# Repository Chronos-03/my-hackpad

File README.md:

# My Custom Hackpad

**Description:** This is a custom 4x2 macropad powered by a Seeed Studio XIAO RP2040. It features a rotary encoder, a 0.91" OLED display, per-key RGB backlighting, and underglow, all wrapped in a custom 3D-printed snap-fit case.

## 📸 Overall Design

## ⚡ KiCAD Schematic & PCB Layout

## 🛠️ Case Assembly & Fit

## 📋 Bill of Materials (BOM)
* 1x Seeed Studio XIAO RP2040
* 8x Mechanical Key Switches (e.g., Gateron)
* 1x 0.91" I2C OLED Display (4-pin)
* 1x Alps Rotary Encoder
* 8x SK6812MINI-E RGB LEDs (Per-key backlight)
* 4x RGB LEDs (Underglow)
* 9x 1N4148 Diodes
* 1x 3D Printed Top Plate
* 1x 3D Printed Bottom Case

## 📐 Hardware Specifications & Layout Map

| Component Category | Designation | Description / Model | X Position (mm) | Y Position (mm) |
| :--- | :--- | :--- | :--- | :--- |
| **Microcontroller** | `U1` | Seeed Studio XIAO | 50.0 | 12.0 |
| **Display Header** | `J1` | 4-Pin OLED (`GND-VCC-SCL-SDA`) | 14.5 | 16.5 |
| **Rotary Encoder** | `SW9` | Alps Rotary Encoder | 79.0 | 19.0 |
| **Key Switch** | `SW1` | Mechanical Key Switch (R1, C1) | 20.0 | 45.35 |
| **Key Switch** | `SW2` | Mechanical Key Switch (R1, C2) | 42.0 | 45.35 |
| **Key Switch** | `SW3` | Mechanical Key Switch (R1, C3) | 64.0 | 45.35 |
| **Key Switch** | `SW4` | Mechanical Key Switch (R1, C4) | 86.0 | 45.35 |
| **Key Switch** | `SW5` | Mechanical Key Switch (R2, C1) | 20.0 | 74.35 |
| **Key Switch** | `SW6` | Mechanical Key Switch (R2, C2) | 42.0 | 74.35 |
| **Key Switch** | `SW7` | Mechanical Key Switch (R2, C3) | 64.0 | 74.35 |
| **Key Switch** | `SW8` | Mechanical Key Switch (R2, C4) | 86.0 | 74.35 |
| **Backlight LED** | `D2` | SK6812MINI-E (SW1) | 16.0 | 38.0 |
| **Backlight LED** | `D3` | SK6812MINI-E (SW2) | 39.0 | 38.0 |
| **Backlight LED** | `D4` | SK6812MINI-E (SW3) | 61.0 | 38.0 |
| **Backlight LED** | `D5` | SK6812MINI-E (SW4) | 85.0 | 38.0 |
| **Backlight LED** | `D6` | SK6812MINI-E (SW5) | 16.0 | 67.0 |
| **Backlight LED** | `D7` | SK6812MINI-E (SW6) | 39.0 | 67.0 |
| **Backlight LED** | `D8` | SK6812MINI-E (SW7) | 61.0 | 67.0 |
| **Backlight LED** | `D9` | SK6812MINI-E (SW8) | 85.0 | 67.0 |
| **Underglow LED** | `D1` | Underglow LED 1 | 14.0 | 5.0 |
| **Underglow LED** | `D10` | Underglow LED 2 | 85.0 | 5.0 |
| **Underglow LED** | `D11` | Underglow LED 3 | 16.0 | 5.0 |
| **Underglow LED** | `D12` | Underglow LED 4 | 85.0 | 95.0 |
| **Matrix Diode** | `Diode 1` | 1N4148 Diode 1 | 18.0 | 21.0 |
| **Matrix Diode** | `Diode 2` | 1N4148 Diode 2 | 18.0 | 24.0 |
| **Matrix Diode** | `Diode 3` | 1N4148 Diode 3 | 18.0 | 27.0 |
| **Matrix Diode** | `Diode 4` | 1N4148 Diode 4 | 18.0 | 30.0 |
| **Matrix Diode** | `Diode 5` | 1N4148 Diode 5 | 35.8 | 21.6 |
| **Matrix Diode** | `Diode 6` | 1N4148 Diode 6 | 35.8 | 24.6 |
| **Matrix Diode** | `Diode 7` | 1N4148 Diode 7 | 35.8 | 27.6 |
| **Matrix Diode** | `Diode 8` | 1N4148 Diode 8 | 35.8 | 30.6 |
| **Matrix Diode** | `Diode 9` | 1N4148 Diode 9 | 64.0 | 25.0 |
| **Mounting Hole** | `H1` | Top-Left Mounting Hole | 5.0 | 5.0 |
| **Mounting Hole** | `H2` | Top-Right Mounting Hole | 95.0 | 5.0 |
| **Mounting Hole** | `H3` | Bottom-Left Mounting Hole | 5.0 | 95.0 |
| **Mounting Hole** | `H4` | Bottom-Right Mounting Hole | 95.0 | 95.0 |

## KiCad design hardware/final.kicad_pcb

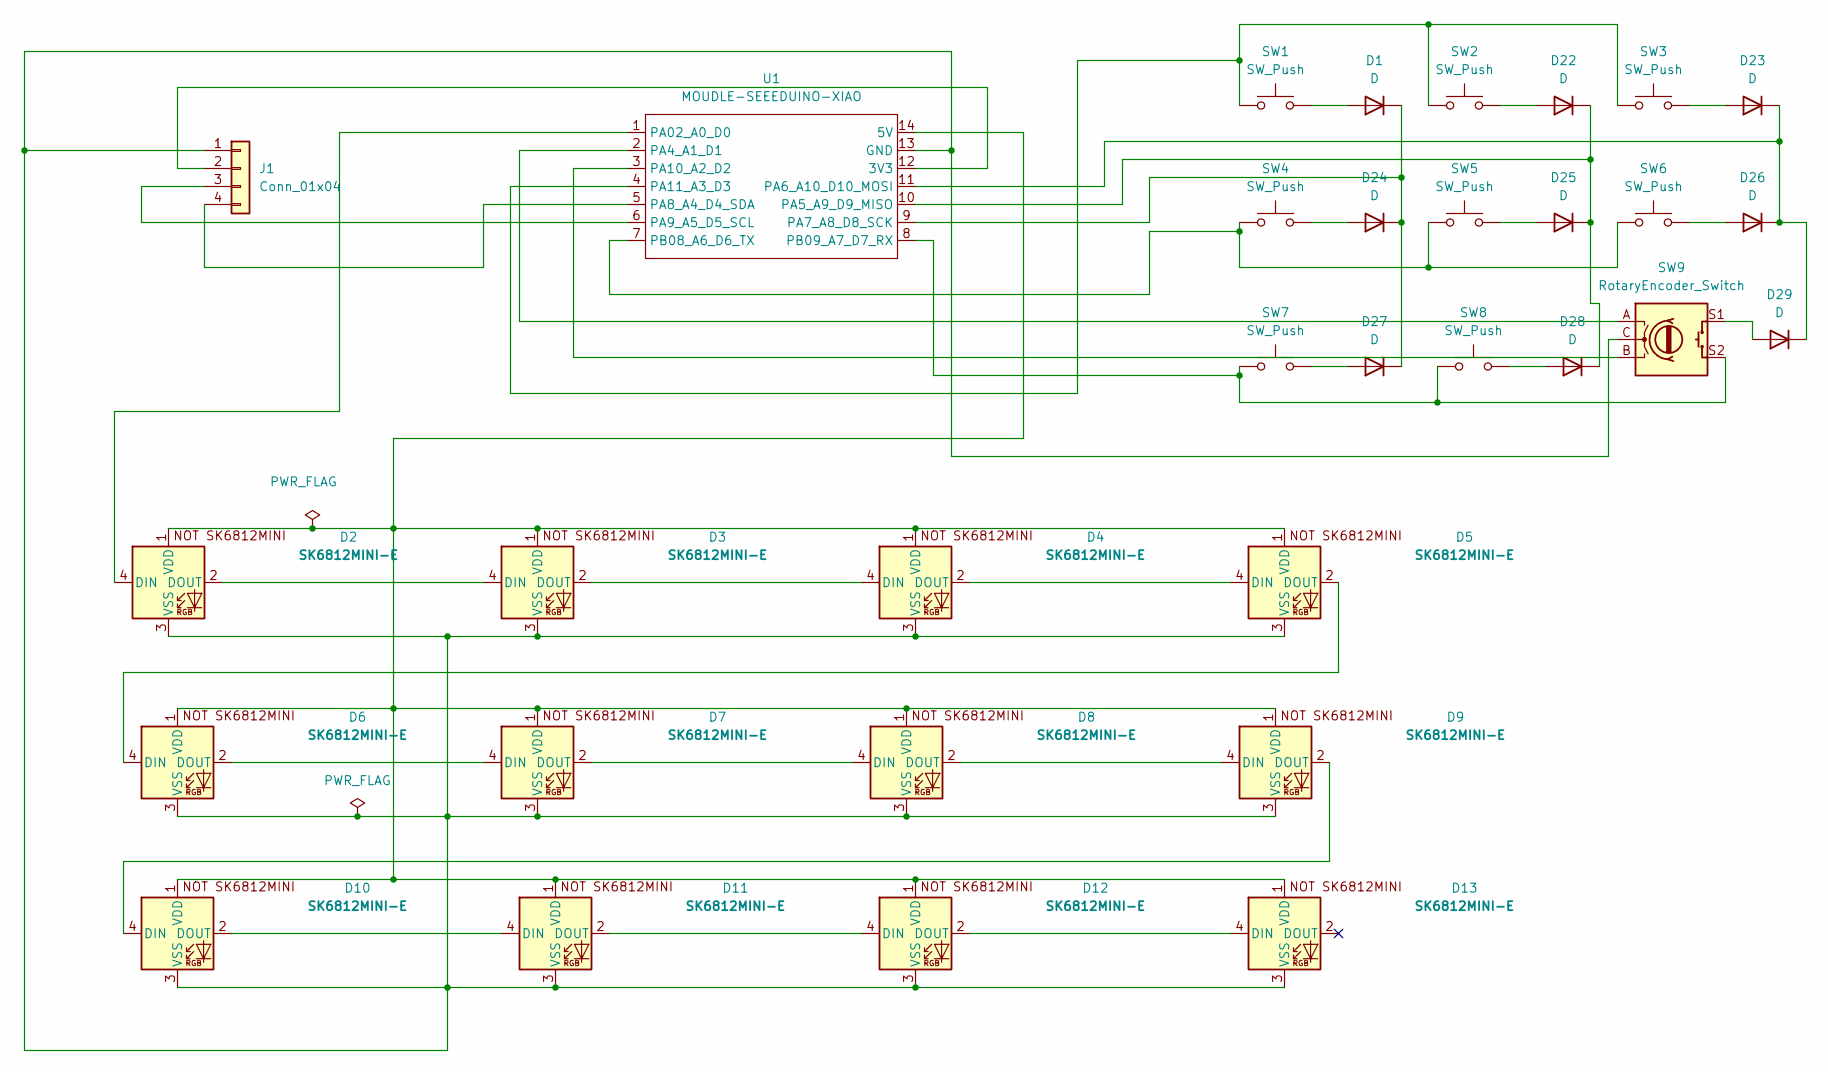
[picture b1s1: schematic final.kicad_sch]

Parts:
D1, D22, D23, D24, D25, D26, D27, D28, D29: D; D_DO-35_SOD27_P7.62mm_Horizontal
D2, D3, D4, D5, D6, D7, D8, D9, D10, D11, D12, D13: SK6812MINI-E; SK6812MINI-E_fixed
J1: Conn_01x04; FanPinHeader_1x04_P2.54mm_Vertical
SW1, SW2, SW3, SW4, SW5, SW6, SW7, SW8: SW_Push; SW_Cherry_MX_1.00u_PCB
SW9: RotaryEncoder_Switch; RotaryEncoder_Alps_EC11E-Switch_Vertical_H20mm
U1: MOUDLE-SEEEDUINO-XIAO; XIAO-Generic-Hybrid-14P-2.54-21X17.8MM

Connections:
unnamed: D1.2 (A), SW1.2
unnamed: D1.1 (K), D24.1 (K), D27.1 (K), U1.9 (PA7_A8_D8_SCK)
unnamed: D2.4 (DIN), U1.1 (PA02_A0_D0)
unnamed: D2.2 (DOUT), D3.4 (DIN)
unnamed: D3.2 (DOUT), D4.4 (DIN)
unnamed: D4.2 (DOUT), D5.4 (DIN)
unnamed: D5.2 (DOUT), D6.4 (DIN)
unnamed: D6.2 (DOUT), D7.4 (DIN)
unnamed: D7.2 (DOUT), D8.4 (DIN)
unnamed: D8.2 (DOUT), D9.4 (DIN)
unnamed: D9.2 (DOUT), D10.4 (DIN)
unnamed: D10.2 (DOUT), D11.4 (DIN)
unnamed: D2.1 (VDD), D3.1 (VDD), D4.1 (VDD), D5.1 (VDD), D6.1 (VDD), D7.1 (VDD), D8.1 (VDD), D9.1 (VDD), D10.1 (VDD), D11.1 (VDD), D12.1 (VDD), D13.1 (VDD), U1.14 (5V)
unnamed: D2.3 (VSS), D3.3 (VSS), D4.3 (VSS), D5.3 (VSS), D6.3 (VSS), D7.3 (VSS), D8.3 (VSS), D9.3 (VSS), D10.3 (VSS), D11.3 (VSS), D12.3 (VSS), D13.3 (VSS), J1.1, SW9.C, U1.13 (GND)
unnamed: D11.2 (DOUT), D12.4 (DIN)
unnamed: D12.2 (DOUT), D13.4 (DIN)
unnamed: D22.2 (A), SW2.2
unnamed: D22.1 (K), D25.1 (K), D28.1 (K), U1.10 (PA5_A9_D9_MISO)
unnamed: D23.2 (A), SW3.2
unnamed: D23.1 (K), D26.1 (K), D29.1 (K), U1.11 (PA6_A10_D10_MOSI)
unnamed: D24.2 (A), SW4.2
unnamed: D25.2 (A), SW5.2
unnamed: D26.2 (A), SW6.2
unnamed: D27.2 (A), SW7.2
unnamed: D28.2 (A), SW8.2
unnamed: D29.2 (A), SW9.S1
unnamed: J1.2, U1.12 (3V3)
unnamed: J1.3, U1.6 (PA9_A5_D5_SCL)
unnamed: J1.4, U1.5 (PA8_A4_D4_SDA)
unnamed: SW9.A, U1.2 (PA4_A1_D1)
unnamed: SW9.B, U1.3 (PA10_A2_D2)
unnamed: SW1.1, SW2.1, SW3.1, U1.4 (PA11_A3_D3)
unnamed: SW4.1, SW5.1, SW6.1, U1.7 (PB08_A6_D6_TX)
unnamed: SW7.1, SW8.1, SW9.S2, U1.8 (PB09_A7_D7_RX)

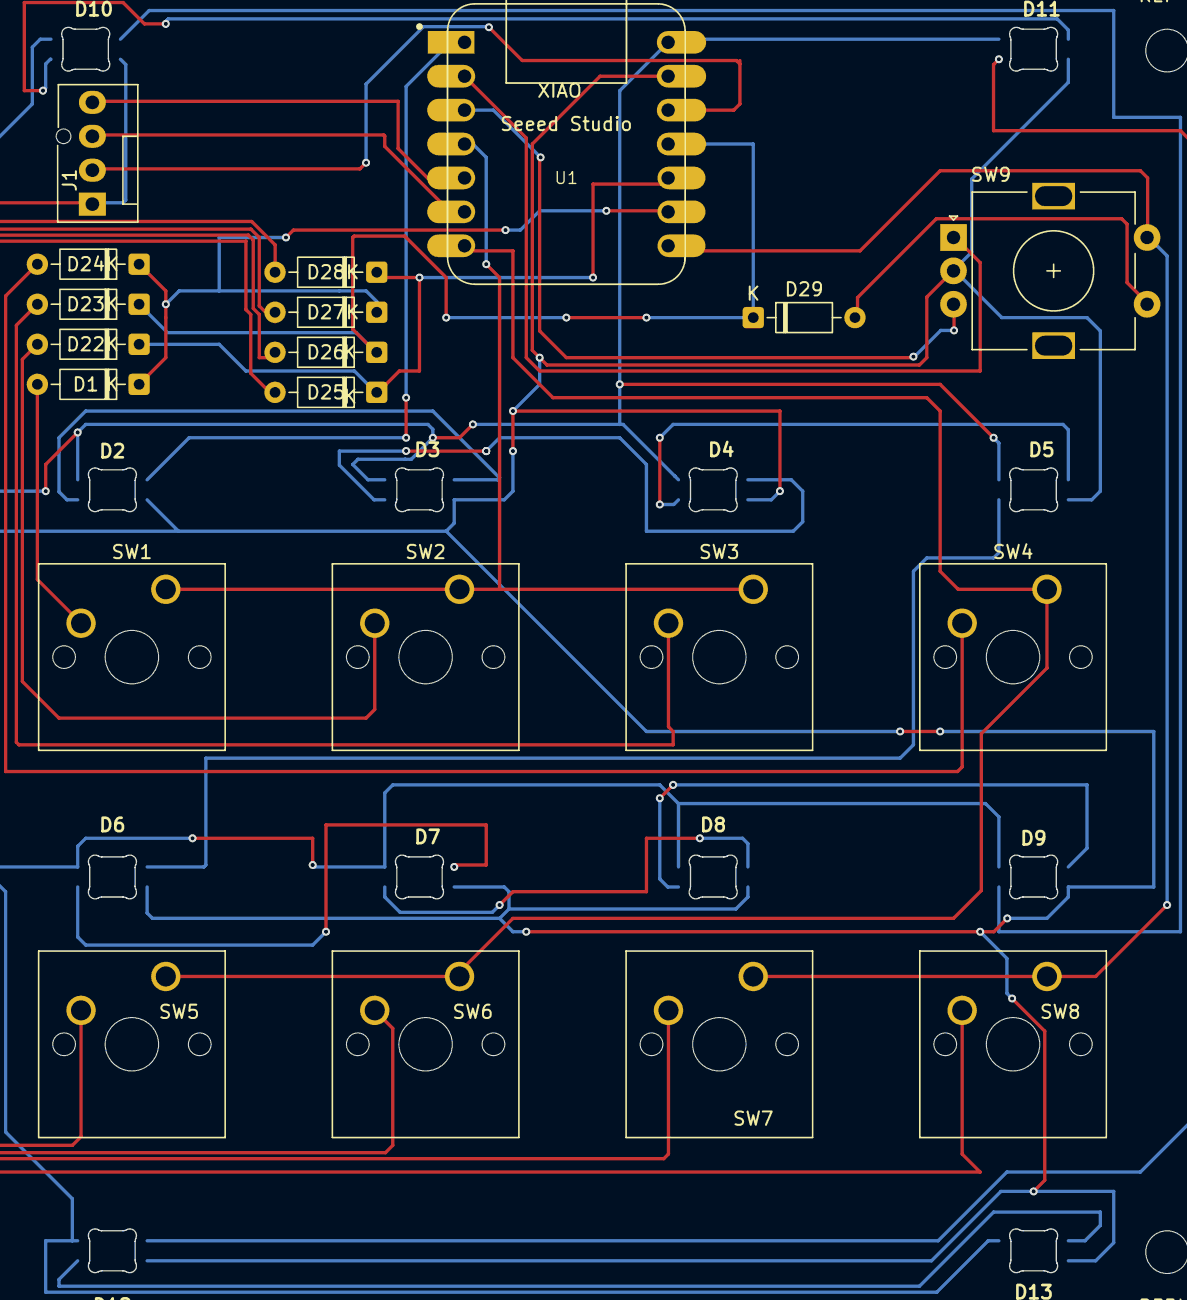
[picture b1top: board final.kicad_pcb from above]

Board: 2 copper layers, 32 parts (0 on the bottom side), 34 nets.
